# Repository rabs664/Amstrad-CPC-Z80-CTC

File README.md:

# Amstrad CPC Z80 CTC
Simple Z80 CTC board compatible with the Amstrad CPC and MX4 connector.

## Objective
Prototyping board to learn about the Z80 CTC, and how to write Z80 assembly using an Amstrad CPC.

## Background
Part of a number of modular cards using Z80 associated peripherals and the Amstrad CPC.

See also;
[Amstrad CPC 2855 PIO](https://github.com/rabs664/Amstrad-CPC-8255-PIO) and [Amstrad CPC Z80 DART](https://github.com/rabs664/Amstrad-CPC-Z80-DART)

## Backplane
[CPC Amstrad Expansion Backplane by revaldinho](https://github.com/revaldinho/cpc_ram_expansion/wiki/CPC-Expansion-Backplane)

## IO Addressing
The IO Address can be selected using two sets of jumpers (CS_HB and CS_LB), supporting the following base address.

* F8E0 and F8F0
* F9E0 and F9F0
* FAE0 and FAF0
* FBE0 and FBF0

See [CPC Wiki IO Port Summary](https://www.cpcwiki.eu/index.php/I/O_Port_Summary) for a list of known IO ports used on the Amstrad CPC.

## Testing
The Z80 CTC board has been built and simple testing has been completed on an Amstrad CPC 6128.

IEI was tied high (via a 10K resistor).

Test schematic using 74HCT74s is included in the images folder.

This board was also used to provide the Baud Clock for the [Amstrad CPC Z80 DART](https://github.com/rabs664/Amstrad-CPC-Z80-DART).

## PCBs
PCBs are available from [Seeed Studio](https://www.seeedstudio.com/Simple-Z80-CTC-board-compatible-with-the-Amstrad-CPC-and-MX4-connecto-g-1393846).

## Components
This [Digi-Key](https://www.digikey.co.uk/en/mylists/list/0Q38QB2P95) List contains all components excluding the Z80 CTC.

Note the right angled header for the port connections was not available at the time of producing this list but all other components were in stock for shipping immediately.

## Assembler
[RASM](https://github.com/EdouardBERGE/rasm)

## Resources
[Zed80 Website](http://zed80.com/Z80-RETRO/index_Home.html)

[CPCWiki](https://www.cpcwiki.eu/index.php/Main_Page)

Z80 Application by James W Coffron ISBN 0-89588-094-6

## Acknowledgements
[@revaldinho](https://github.com/revaldinho)

Don Prefontaine 

Peter Murray

[@EdouardBERGE](https://github.com/EdouardBERGE)

# Release History
## Version 2.0
* First Release

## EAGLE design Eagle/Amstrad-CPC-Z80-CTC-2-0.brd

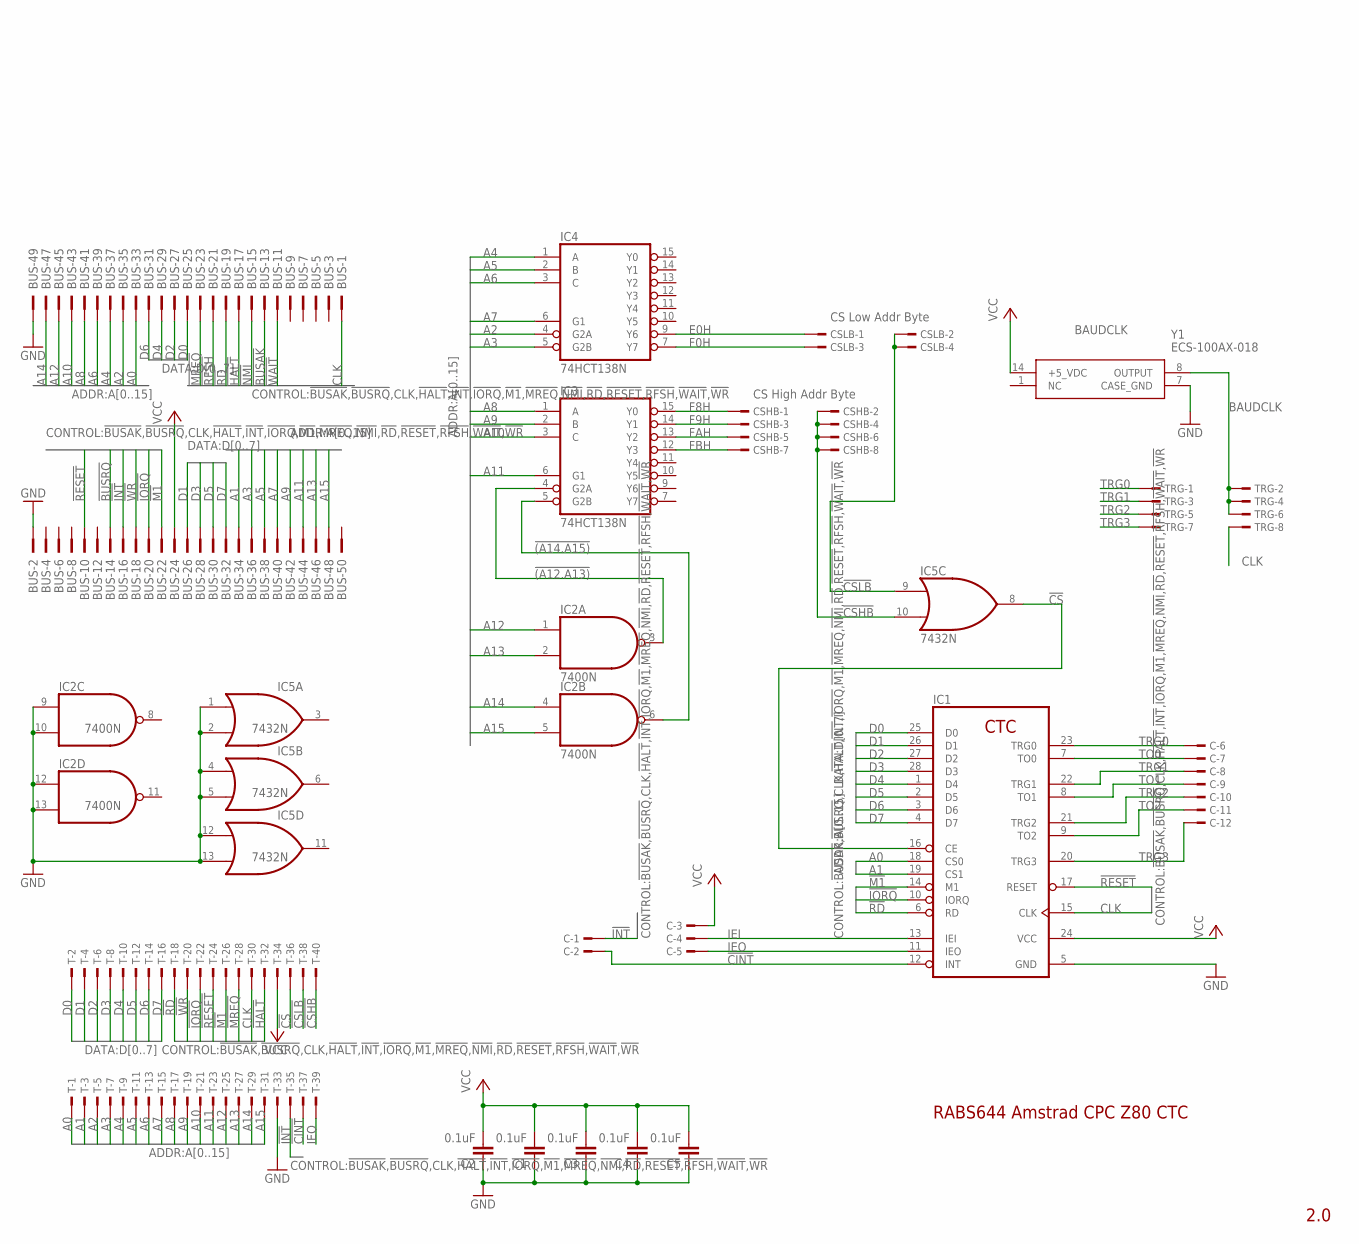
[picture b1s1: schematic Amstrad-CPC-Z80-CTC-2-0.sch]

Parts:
BUS: 2550-; PAK100/2500-50
C: TSW-112-07-G-S; TSW-112-XX-G-S
C1, C2, C3, C4, C5: 0.1uF; C050-025X075
CSHB: TSW-104-07-G-D; TSW-104-XX-G-D
CSLB: TSW-102-07-G-D; TSW-102-XX-G-D
IC1: Z80CTC; DIL28
IC2: 7400N; DIL14
IC3, IC4: 74HCT138N; DIL16
IC5: 7432N; DIL14
T: TSW-120-07-G-D; TSW-120-XX-G-D
TRG: TSW-104-07-G-D; TSW-104-XX-G-D
Y1: ECS-100AX-018; ECS100AX018

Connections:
!(A12.A13): IC2.3 (O), IC3.4 (G2A)
!(A14.A15): IC2.6 (O), IC3.5 (G2B)
!BUSAK: BUS.13
!BUSRQ: BUS.14
!CINT: C.2, IC1.12 (INT), T.37
!CS: IC1.16 (CE), IC5.8 (O), T.36
!CSHB: CSHB.2, CSHB.4, CSHB.6, CSHB.8, IC5.10 (I1), T.40
!CSLB: CSLB.2, CSLB.4, IC5.9 (I0), T.38
!HALT: BUS.17, T.32
!INT: BUS.16, C.1, T.35
!IORQ: BUS.20, IC1.10 (IORQ), T.22
!M1: BUS.22, IC1.14 (M1), T.26
!MREQ: BUS.23, T.28
!NMI: BUS.15
!RD: BUS.19, IC1.6 (RD), T.18
!RESET: BUS.10, IC1.17 (RESET), T.24
!RFSH: BUS.21
!WAIT: BUS.11
!WR: BUS.18, T.20
A0: BUS.33, IC1.18 (CS0), T.1
A1: BUS.34, IC1.19 (CS1), T.3
A2: BUS.35, IC4.4 (G2A), T.5
A3: BUS.36, IC4.5 (G2B), T.7
A4: BUS.37, IC4.1 (A), T.9
A5: BUS.38, IC4.2 (B), T.11
A6: BUS.39, IC4.3 (C), T.13
A7: BUS.40, IC4.6 (G1), T.15
A8: BUS.41, IC3.1 (A), T.17
A9: BUS.42, IC3.2 (B), T.19
A10: BUS.43, IC3.3 (C), T.21
A11: BUS.44, IC3.6 (G1), T.23
A12: BUS.45, IC2.1 (I0), T.25
A13: BUS.46, IC2.2 (I1), T.27
A14: BUS.47, IC2.4 (I0), T.29
A15: BUS.48, IC2.5 (I1), T.31
BAUDCLK: TRG.2, TRG.4, TRG.6, Y1.8 (OUTPUT)
CLK: BUS.1, IC1.15 (CLK), T.30, TRG.8
D0: BUS.25, IC1.25 (D0), T.2
D1: BUS.26, IC1.26 (D1), T.4
D2: BUS.27, IC1.27 (D2), T.6
D3: BUS.28, IC1.28 (D3), T.8
D4: BUS.29, IC1.1 (D4), T.10
D5: BUS.30, IC1.2 (D5), T.12
D6: BUS.31, IC1.3 (D6), T.14
D7: BUS.32, IC1.4 (D7), T.16
E0H: CSLB.1, IC4.9 (Y6)
F0H: CSLB.3, IC4.7 (Y7)
F8H: CSHB.1, IC3.15 (Y0)
F9H: CSHB.3, IC3.14 (Y1)
FAH: CSHB.5, IC3.13 (Y2)
FBH: CSHB.7, IC3.12 (Y3)
GND: BUS.2, BUS.49, C1.1, C2.1, C3.1, C4.1, C5.1, IC1.5 (GND), IC2.7 (GND), IC2.9 (I0), IC2.10 (I1), IC2.12 (I0), IC2.13 (I1), IC3.8 (GND), IC4.8 (GND), IC5.1 (I0), IC5.2 (I1), IC5.4 (I0), IC5.5 (I1), IC5.7 (GND), IC5.12 (I0), IC5.13 (I1), T.33, Y1.7 (CASE_GND)
IEI: C.4, IC1.13 (IEI)
IEO: C.5, IC1.11 (IEO), T.39
TO0: C.7, IC1.7 (TO0)
TO1: C.9, IC1.8 (TO1)
TO2: C.11, IC1.9 (TO2)
TRG0: C.6, IC1.23 (TRG0), TRG.1
TRG1: C.8, IC1.22 (TRG1), TRG.3
TRG2: C.10, IC1.21 (TRG2), TRG.5
TRG3: C.12, IC1.20 (TRG3), TRG.7
VCC: BUS.24, C.3, C1.2, C2.2, C3.2, C4.2, C5.2, IC1.24 (VCC), IC2.14 (VCC), IC3.16 (VCC), IC4.16 (VCC), IC5.14 (VCC), T.34, Y1.14 (+5_VDC)

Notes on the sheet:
2.0
RABS644 Amstrad CPC Z80 CTC
CS Low Addr Byte
CS High Addr Byte
BAUDCLK

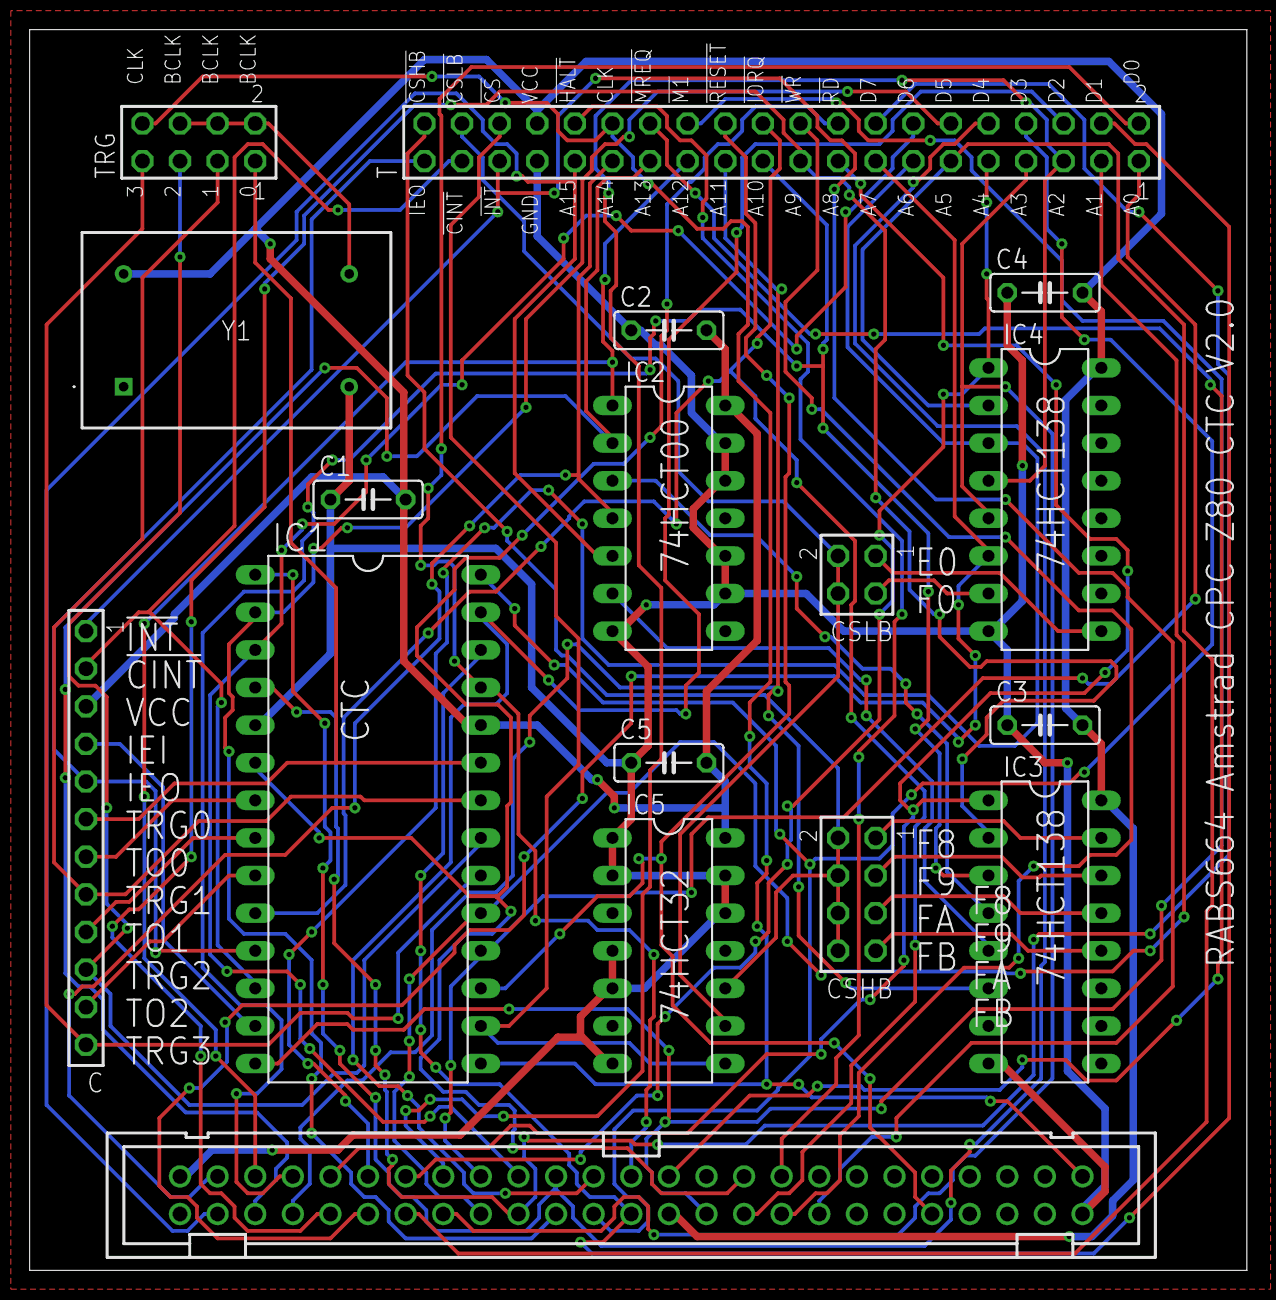
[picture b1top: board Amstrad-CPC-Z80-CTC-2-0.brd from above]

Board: 2 copper layers, 82.2 x 83.8 mm, 17 parts (0 on the bottom side), 57 nets.

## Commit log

2023-08-12 Create Eagle
2023-08-25 Update README.md
    Added Seeed Studio Reference to PCB
